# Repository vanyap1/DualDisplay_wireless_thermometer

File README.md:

# Double display wireless thermometer

The temperature measurement on unit TX is transmitted to the unit RX.
The temperature on both units is displayed.

In unit RX, there is an alarm that works when the communication between the units is lost and the temperature exceeds 85 degrees Celsius.
Also, both units work in the event of a power failure.

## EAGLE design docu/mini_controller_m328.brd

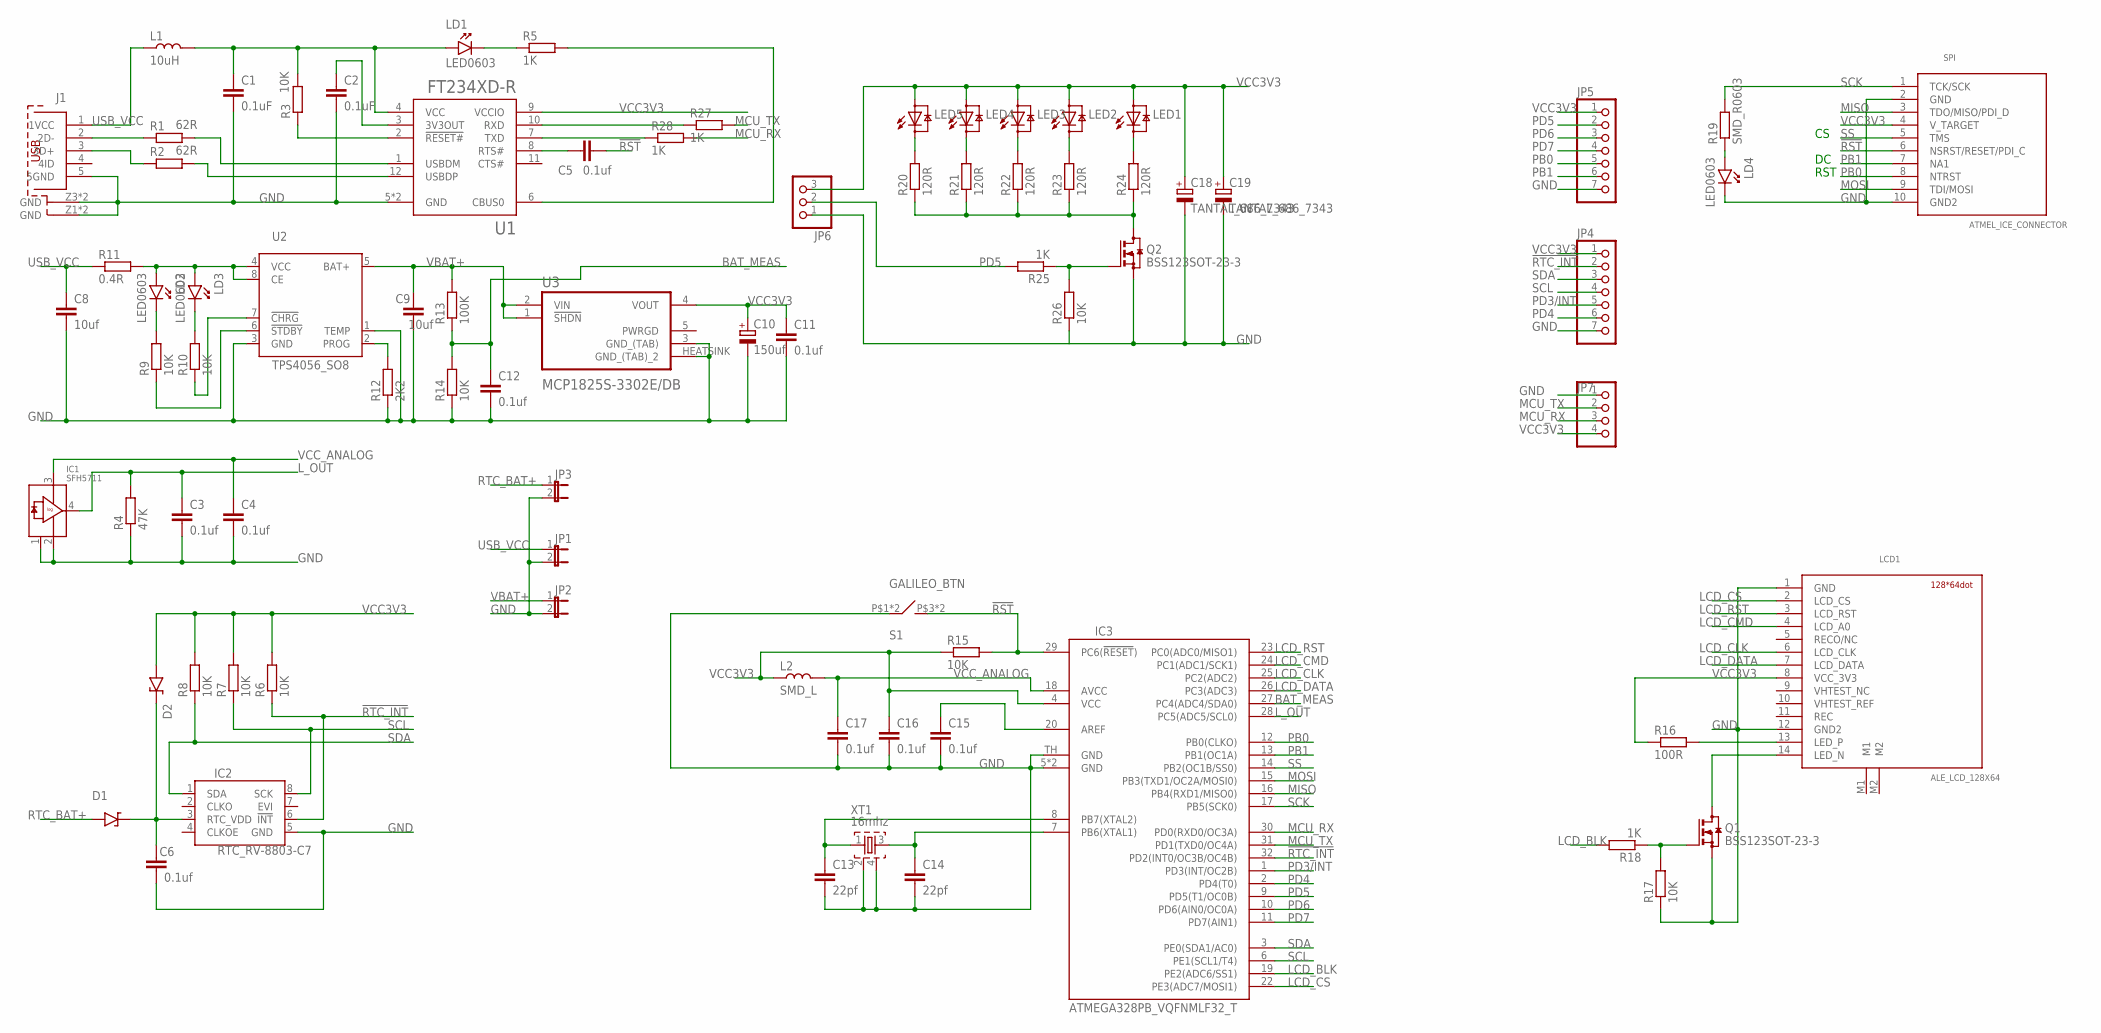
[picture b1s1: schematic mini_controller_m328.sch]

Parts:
C1, C2: 0.1uF; 0603
C3, C4, C5, C6, C11, C12, C15, C16, C17: 0.1uf; 0603
C8, C9: 10uf; 1206
C10: 150uf; KA-3528ASYC
C13, C14: 22pf; 0603
C18, C19: TANTAL_686_7343; D/7343-31R
D1, D2: D_SOD323; SOD-323_D
IC1: SFH5711
IC2: RTC_RV-8803-C7; C7_RTC
IC3: ATMEGA328PB_VQFNMLF32_T; MLF32-TH
J1: MINI_USB_TYP_B_@; 65100516121
JP1, JP2, JP3: JP1E; JP1
JP4, JP5: PINHD-1X7; 1X07
JP6: PINHD-1X3; 1X03
JP7: PINHD-1X4; 1X04
L1: 10uH; 0805
L2: SMD_L; 0805
LCD1: ALE_LCD_128X64; ALE_LCD_14PIN_CONNECTOR
LD1, LD2, LD3, LD4: LED0603; 0603_P
LED1, LED2, LED3, LED4, LED5: GM5BW96385A
Q1, Q2: BSS123SOT-23-3; SOT-23(3)
R1, R2: 62R; 0603
R3, R6, R7, R8, R9, R10, R14, R15, R17, R26: 10K; 0603
R4: 47K; 0603
R5, R18, R25, R27, R28: 1K; 0603
R11: 0.4R; 1206
R12: 2K2; 0603
R13: 100K; 0603
R16: 100R; 0603
R19: SMD_R0603; 0603
R20, R21, R22, R23, R24: 120R; 1206
S1: GALILEO_BTN; GALILEO_VERT_BTN
SPI: ATMEL_ICE_CONNECTOR; MINI10P_SPI/JTAG/PDI
U1: FT234XD-R; IC_FT234XD-R
U2: TPS4056_SO8; SO8
U3: MCP1825S-3302E/DB; SOT230P700X180-4N
XT1: 16mhz; QUARTZ_3X3MM

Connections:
!CHRG: R10.1, U2.7 (!CHRG)
!RST: C5.2, IC3.29 (PC6(!RESET!)), R15.2, S1.P$3 (4), S1.P$4 (4), SPI.6 (NSRST/RESET/PDI_C)
!RTC_INT: IC2.6 (!INT), IC3.32 (PD2(INT0/OC3B/OC4B)), JP4.2, R6.1
BAT_MEAS: C12.1, IC3.27 (PC4(ADC4/SDA0)), R13.1, R14.2
DM1: J1.2 (2D-), R1.1
DM2: R1.2, U1.1 (USBDM)
DP1: J1.3 (3D+), R2.1
DP2: R2.2, U1.12 (USBDP)
GND: C1.2, C2.2, C3.2, C4.2, C6.2, C8.2, C9.2, C10.M (-), C11.2, C12.2, C13.2, C14.2, C15.2, C16.2, C17.2, C18.-, C19.-, IC1.1, IC1.2, IC2.5 (GND), IC3.5 (GND), IC3.21 (GND), IC3.TH (GND), J1.5 (5GND), J1.Z1 (GND), J1.Z2 (GND), J1.Z3 (GND), J1.Z4 (GND), JP1.2, JP2.2, JP3.2, JP4.7, JP5.7, JP6.1, JP7.1, LCD1.1 (GND), LCD1.12 (GND2), LD4.1 (K), Q1.2 (S), Q2.2 (S), R4.1, R12.1, R14.1, R17.1, R26.1, S1.P$1 (1), S1.P$2 (1), SPI.2 (GND), SPI.10 (GND2), U1.5 (GND), U1.13 (GND), U2.1 (TEMP), U2.3 (GND), U3.3 (GND_(TAB)), U3.HEATSINK (GND_(TAB)_2), XT1.2, XT1.4
LCD_BLK: IC3.19 (PE2(ADC6/SS1)), R18.2
LCD_CLK: IC3.25 (PC2(ADC2)), LCD1.6 (LCD_CLK)
LCD_CMD: IC3.24 (PC1(ADC1/SCK1)), LCD1.4 (LCD_A0)
LCD_CS: IC3.22 (PE3(ADC7/MOSI1)), LCD1.2 (LCD_CS)
LCD_DATA: IC3.26 (PC3(ADC3)), LCD1.7 (LCD_DATA)
LCD_RST: IC3.23 (PC0(ADC0/MISO1)), LCD1.3 (LCD_RST)
L_OUT: C3.1, IC1.4, IC3.28 (PC5(ADC5/SCL0)), R4.2
MCU_RX: IC3.30 (PD0(RXD0/OC3A)), JP7.3, R28.2
MCU_TX: IC3.31 (PD1(TXD0/OC4A)), JP7.2, R27.2
MISO: IC3.16 (PB4(RXD1/MISO0)), SPI.3 (TDO/MISO/PDI_D)
MOSI: IC3.15 (PB3(TXD1/OC2A/MOSI0)), SPI.9 (TDI/MOSI)
unnamed: LCD1.13 (LED_P), R16.2
unnamed: LCD1.14 (LED_N), Q1.3 (D)
unnamed: R9.1, U2.6 (!STDBY)
unnamed: Q1.1 (G), R17.2, R18.1
unnamed: LD2.1 (K), R9.2
unnamed: LD3.1 (K), R10.2
unnamed: C1.1, L1.2, LD1.2 (A), R3.2, U1.4 (VCC)
unnamed: C13.1, IC3.8 (PB7(XTAL2)), XT1.1
unnamed: C2.1, U1.3 (3V3OUT)
unnamed: LD1.1 (K), R5.1
unnamed: R5.2, U1.6 (CBUS0)
unnamed: C14.1, IC3.7 (PB6(XTAL1)), XT1.3
unnamed: LD2.2 (A), LD3.2 (A), R11.2, U2.4 (VCC), U2.8 (CE)
unnamed: R27.1, U1.10 (RXD)
unnamed: C5.1, U1.8 (RTS#)
unnamed: LD4.2 (A), R19.1
unnamed: LED5.C, R20.2
unnamed: R12.2, U2.2 (PROG)
unnamed: C6.1, D1.K, D2.K, IC2.3 (RTC_VDD)
unnamed: C15.1, IC3.20 (AREF)
unnamed: LED4.C, R21.2
unnamed: LED3.C, R22.2
unnamed: LED2.C, R23.2
unnamed: LED1.C, R24.2
unnamed: Q2.1 (G), R25.1, R26.2
unnamed: Q2.3 (D), R20.1, R21.1, R22.1, R23.1, R24.1
unnamed: R28.1, U1.7 (TXD)
PB0: IC3.12 (PB0(CLKO)), JP5.5, SPI.8 (NTRST)
PB1: IC3.13 (PB1(OC1A)), JP5.6, SPI.7 (NA1)
PD3/INT: IC3.1 (PD3(INT/OC2B)), JP4.5
PD4: IC3.2 (PD4(T0)), JP4.6
PD5: IC3.9 (PD5(T1/OC0B)), JP5.2, JP6.2, R25.2
PD6: IC3.10 (PD6(AIN0/OC0A)), JP5.3
PD7: IC3.11 (PD7(AIN1)), JP5.4
RTC_BAT+: D1.A, JP3.1
SCK: IC3.17 (PB5(SCK0)), R19.2, SPI.1 (TCK/SCK)
SCL: IC2.8 (SCK), IC3.6 (PE1(SCL1/T4)), JP4.4, R7.1
SDA: IC2.1 (SDA), IC3.3 (PE0(SDA1/AC0)), JP4.3, R8.1
SER_RST: R3.1, U1.2 (!RESET#)
SS: IC3.14 (PB2(OC1B/SS0)), SPI.5 (TMS)
USB_VCC: C8.1, J1.1 (1VCC), JP1.1, L1.1, R11.1
VBAT+: C9.1, JP2.1, R13.2, U2.5 (BAT+), U3.1 (!SHDN), U3.2 (VIN)
VCC3V3: C10.P (+), C11.1, C16.1, C18.+, C19.+, D2.A, IC3.4 (VCC), JP4.1, JP5.1, JP6.3, JP7.4, L2.1, LCD1.8 (VCC_3V3), LED1.A, LED2.A, LED3.A, LED4.A, LED5.A, R6.2, R7.2, R8.2, R15.1, R16.1, SPI.4 (V_TARGET), U1.9 (VCCIO), U3.4 (VOUT)
VCC_ANALOG: C4.1, C17.1, IC1.3, IC3.18 (AVCC), L2.2

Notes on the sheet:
RST

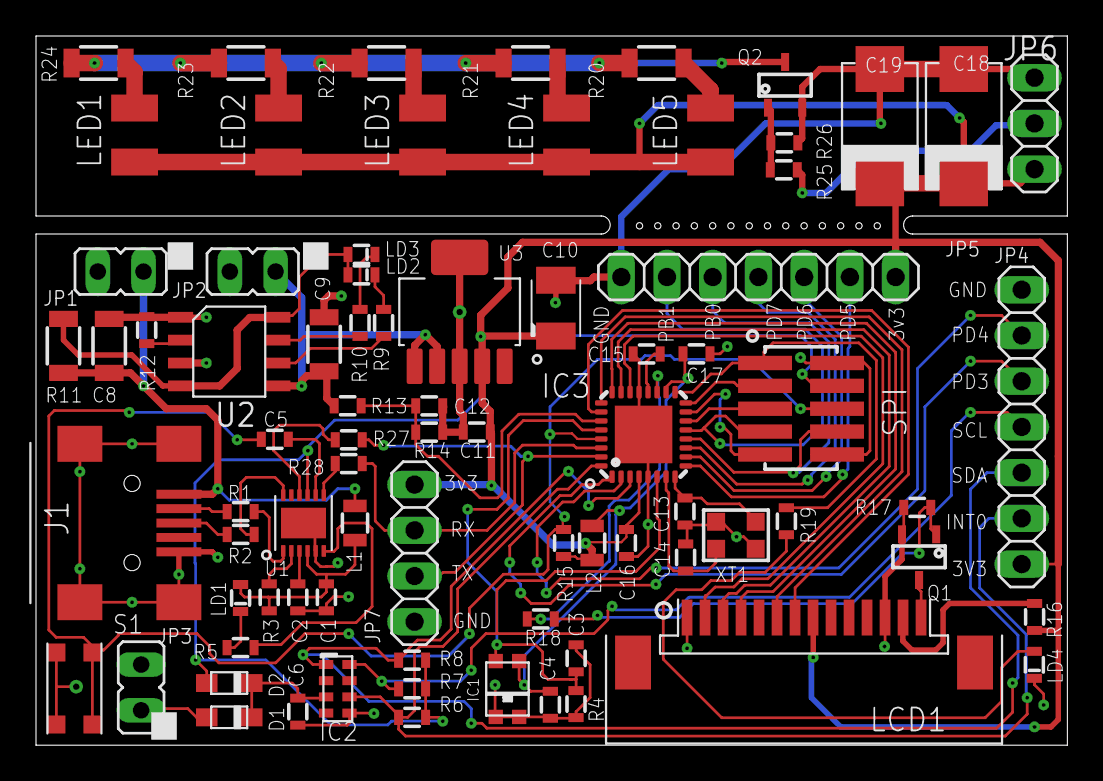
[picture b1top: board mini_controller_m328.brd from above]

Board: 2 copper layers, 57.3 x 39.4 mm, 79 parts (0 on the bottom side), 64 nets.

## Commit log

2023-08-04 TX Unit was released
2023-08-04 Added RX unit, and clean project
2023-08-05 added RX unit code. Need to add data valid timer, for checking when data isn't valid or broken
2023-08-06 Prereleased commit
2023-08-06 Project pictures added
2023-08-10 added watchdog to RX module
2023-08-11 addeded watchadog to TX module
